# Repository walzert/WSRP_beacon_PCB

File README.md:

# Yet another WSPR beacon based on SI5351

I just wanted to make a PCB for ham radio purpose and here is the PCB  part.

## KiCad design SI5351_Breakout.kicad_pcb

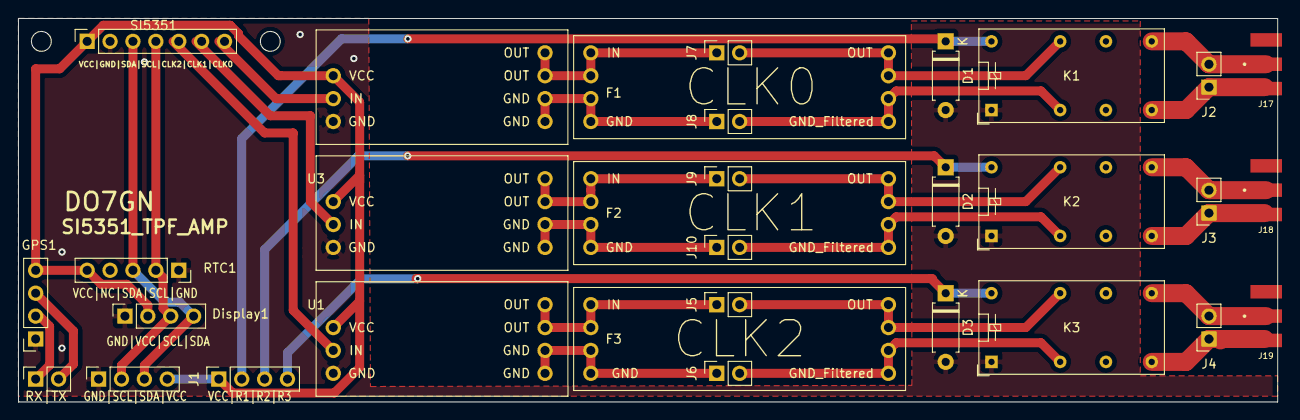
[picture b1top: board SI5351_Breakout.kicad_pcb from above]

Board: 2 copper layers, 139.7 x 42.5 mm, 31 parts (0 on the bottom side), 30 nets.

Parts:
Arduino1: Arduino; PinSocket_1x04_P2.54mm_Vertical
D1, D2, D3: D; D_A-405_P7.62mm_Horizontal
Display1: Display; PinSocket_1x04_P2.54mm_Vertical
F1: TPF_0; TPF
F2: TPF_1; TPF
F3: TPF_2; TPF
GPS1: GPS; PinSocket_1x04_P2.54mm_Vertical
J1: Conn_01x03_Female; PinSocket_1x04_P2.54mm_Vertical
J2, J3, J4, J5, J6, J7, J8, J9, J10: Conn_01x02_Female; PinSocket_1x02_P2.54mm_Vertical
J17, J18, J19: CON-SMA-EDGE-S; RFSOLUTIONS_CON-SMA-EDGE-S
K1, K2, K3: G5V-2; Relay_DPDT_Omron_G5V-2
RTC1: RTC; PinSocket_1x05_P2.54mm_Vertical
RX|TX: ArduinoRXTX; PinSocket_1x02_P2.54mm_Vertical
SI5351: SI5351; PinSocket_1x07_P2.54mm_Vertical
U1, U2, U3: AMP

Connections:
GND: Arduino1.1, D1.2, D2.2, D3.2, Display1.1, GPS1.1, K1.1, K2.1, K3.1, RTC1.1, SI5351.2, U1.3, U2.3, U3.3
GND_CLK0_OUT: J2.1, J17.G1, J17.G2, J17.G3, J17.G4, K1.8
GND_CLK1_OUT: J3.1, J18.G1, J18.G2, J18.G3, J18.G4, K2.8
GND_CLK2_OUT: J4.1, J19.G1, J19.G2, J19.G3, J19.G4, K3.8
RX: GPS1.2, RX|TX.1
Relay_0: D1.1, J1.2, K1.16
Relay_1: D2.1, J1.3, K2.16
Relay_2: D3.1, J1.4, K3.16
SCL: Arduino1.2, Display1.3, RTC1.2, SI5351.4
SDA: Arduino1.3, Display1.4, RTC1.3, SI5351.3
SIGNAL_CLK0: SI5351.7, U3.2
SIGNAL_CLK0_OUT: J2.2, J17.1, K1.9
SIGNAL_CLK1: SI5351.6, U1.2
SIGNAL_CLK1_OUT: J3.2, J18.1, K2.9
SIGNAL_CLK2: SI5351.5, U2.2
SIGNAL_CLK2_OUT: J4.2, J19.1, K3.9
TPF_0_IN+: F1.1, F1.2, J7.1, U3.6, U3.7
TPF_0_IN-: F1.3, F1.4, J8.1, U3.4, U3.5
TPF_1_IN+: F2.1, F2.2, J9.1, U1.6, U1.7
TPF_1_IN-: F2.3, F2.4, J10.1, U1.4, U1.5
TPF_2_IN+: F3.1, F3.2, J5.1, U2.6, U2.7
TPF_2_IN-: F3.3, F3.4, J6.1, U2.4, U2.5
TP_0_Relay_OUT+: F1.7, F1.8, J7.2, K1.13
TP_0_Relay_OUT-: F1.5, F1.6, J8.2, K1.4
TP_1_Relay_OUT+: F2.7, F2.8, J9.2, K2.13
TP_1_Relay_OUT-: F2.5, F2.6, J10.2, K2.4
TP_2_Relay_OUT+: F3.7, F3.8, J5.2, K3.13
TP_2_Relay_OUT-: F3.5, F3.6, J6.2, K3.4
TX: GPS1.3, RX|TX.2
VCC: Arduino1.4, Display1.2, GPS1.4, J1.1, RTC1.5, SI5351.1, U1.1, U2.1, U3.1

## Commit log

2021-07-08 Render image
2021-07-08 latest version
2021-07-08 added block diagram for PCB
